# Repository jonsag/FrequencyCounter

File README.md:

# FrequencyCounter

An attempt for a diy frequency counter

## Links

### AE-AQM1602A

* [https://akizukidenshi.com/goodsaffix/AQM1602_rev2.pdf](https://akizukidenshi.com/goodsaffix/AQM1602_rev2.pdf)
* [https://akizukidenshi.com/goodsaffix/AE-AQM1602A_20230417.pdf](https://akizukidenshi.com/goodsaffix/AE-AQM1602A_20230417.pdf)
* [https://akizukidenshi.com/catalog/g/g108779](https://akizukidenshi.com/catalog/g/g108779)

### Pico GFX Pack - LCD 128x64px

* [https://www.electrokit.com/pico-gfx-pack-lcd-128x64px](https://www.electrokit.com/pico-gfx-pack-lcd-128x64px)
* [https://www.electrokit.com/upload/product/41020/41020660/GFX_pack_schematic.pdf](https://www.electrokit.com/upload/product/41020/41020660/GFX_pack_schematic.pdf)
*

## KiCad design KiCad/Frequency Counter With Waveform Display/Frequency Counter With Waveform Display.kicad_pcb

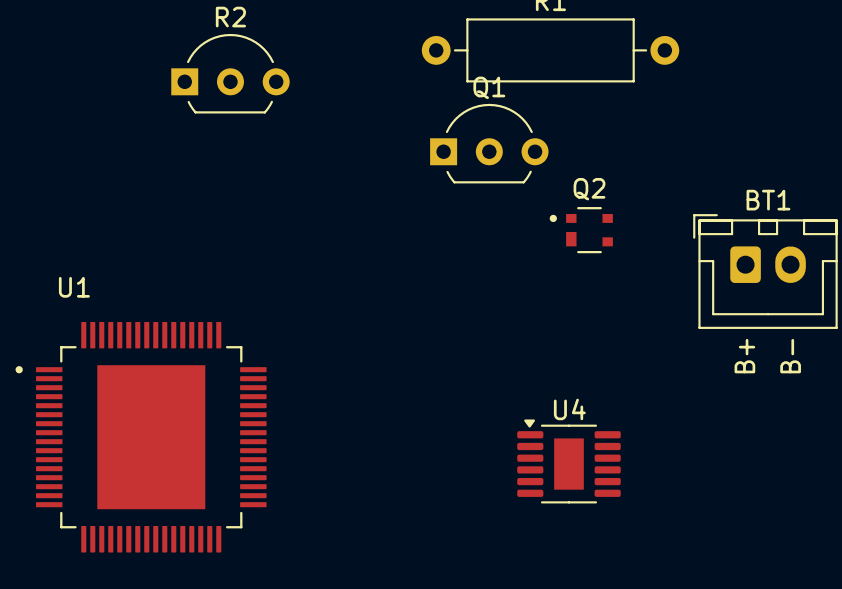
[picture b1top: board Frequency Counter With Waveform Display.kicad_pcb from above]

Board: 2 copper layers, 7 parts (0 on the bottom side), 10 nets, no tracks yet.

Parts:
BT1: Battery; 2-pin JST Battery In
Q1: BF245B; TO-92L_Inline_Wide
Q2: BGA420; INFINEON_BFP540
R1: 1M2; R_Axial_DIN0309_L9.0mm_D3.2mm_P12.70mm_Horizontal
R2: 390R; TO-92L_Inline_Wide
U1: PIC24FJ64GC006-I/PT; QFP50P1200X1200X120-65N
U4: LTC3245xMSE; MSOP-12-1EP_3x4.039mm_P0.65mm_EP1.651x2.845mm

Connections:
+3.3V: U1.10 (VDD), U1.19 (AVDD), U1.26 (SVDD), U1.38 (VDD)
/BufferdVref: U1.11 (RB5), U1.24 (CH1+)
/Input/A1: Q1.3 (D), R2.2
/T1CK: U1.27 (RB12/T1CK), U1.31 (RF4)
/Vref: U1.4 (RG6), U1.8 (RG9)
GND: Q2.2 (E), R1.2, U1.9 (VSS), U1.20 (AVSS), U1.25 (CH1-), U1.41 (VSS), U4.4 (~BURST), U4.12 (GND), U4.13 (EP)
unnamed: BT1.1 (+), U4.1 (VIN), U4.2 (VIN), U4.3 (VIN)
unnamed: Q1.1 (G), R1.1
unnamed: U4.5 (SEL1), U4.6 (SEL2)
unnamed: U4.7 (OUTS/ADJ), U4.10 (VOUT)

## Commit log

2025-01-31 Readme
